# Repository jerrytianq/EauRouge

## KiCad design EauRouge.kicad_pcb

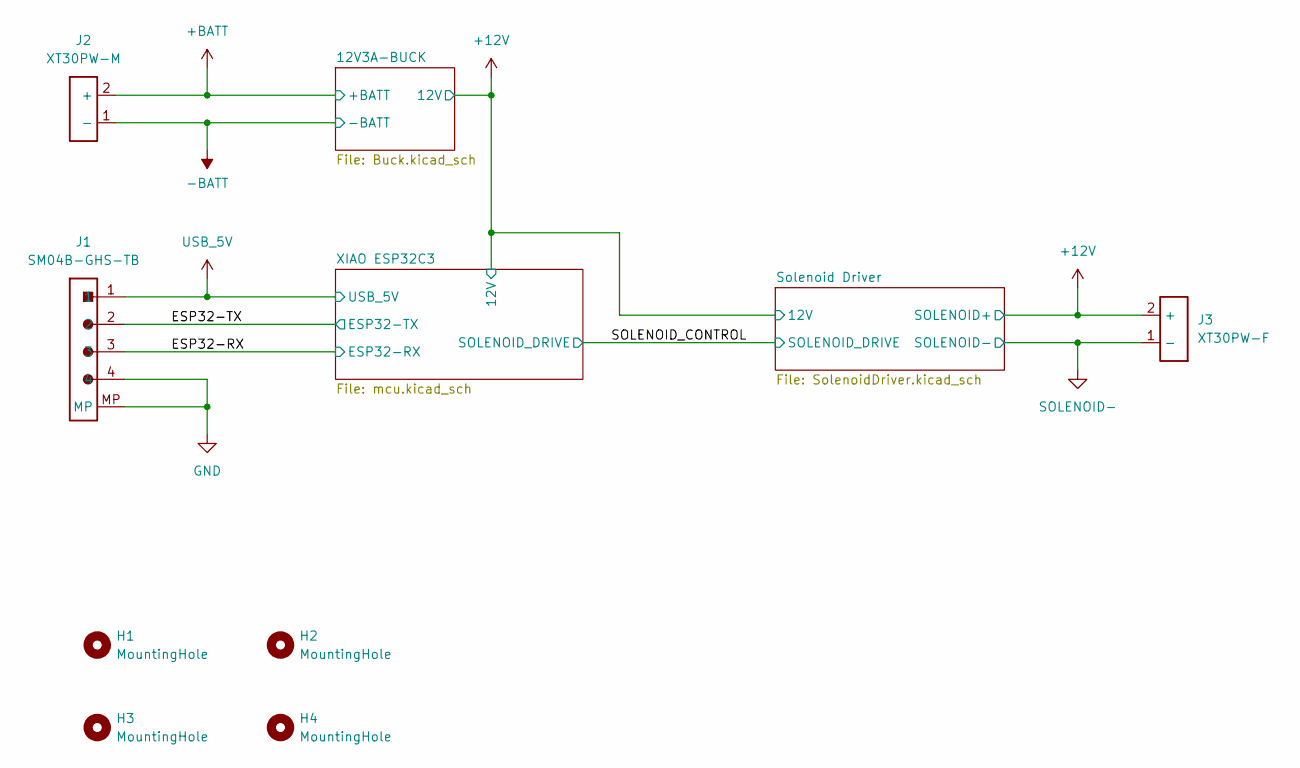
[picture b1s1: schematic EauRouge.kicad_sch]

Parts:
H1, H2, H3, H4: MountingHole; MountingHole_3.2mm_M3
J1: SM04B-GHS-TB; JST_GH_SM04B-GHS-TB_1x04-1MP_P1.25mm_Horizontal
J2: XT30PW-M; AMASS_XT30PW-M_1x02_P2.50mm_Horizontal
J3: XT30PW-F; AMASS_XT30PW-F_1x02_P2.50mm_Horizontal

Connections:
+12V: J3.2 (+); also elsewhere on the board
+BATT: J2.2 (+); also elsewhere on the board
-BATT: J2.1 (-); also elsewhere on the board
/ESP32-RX: J1.3; also elsewhere on the board
/ESP32-TX: J1.2; also elsewhere on the board
GND: J1.4, J1.MP; also elsewhere on the board
SOLENOID-: J3.1 (-); also elsewhere on the board
USB_5V: J1.1; also elsewhere on the board

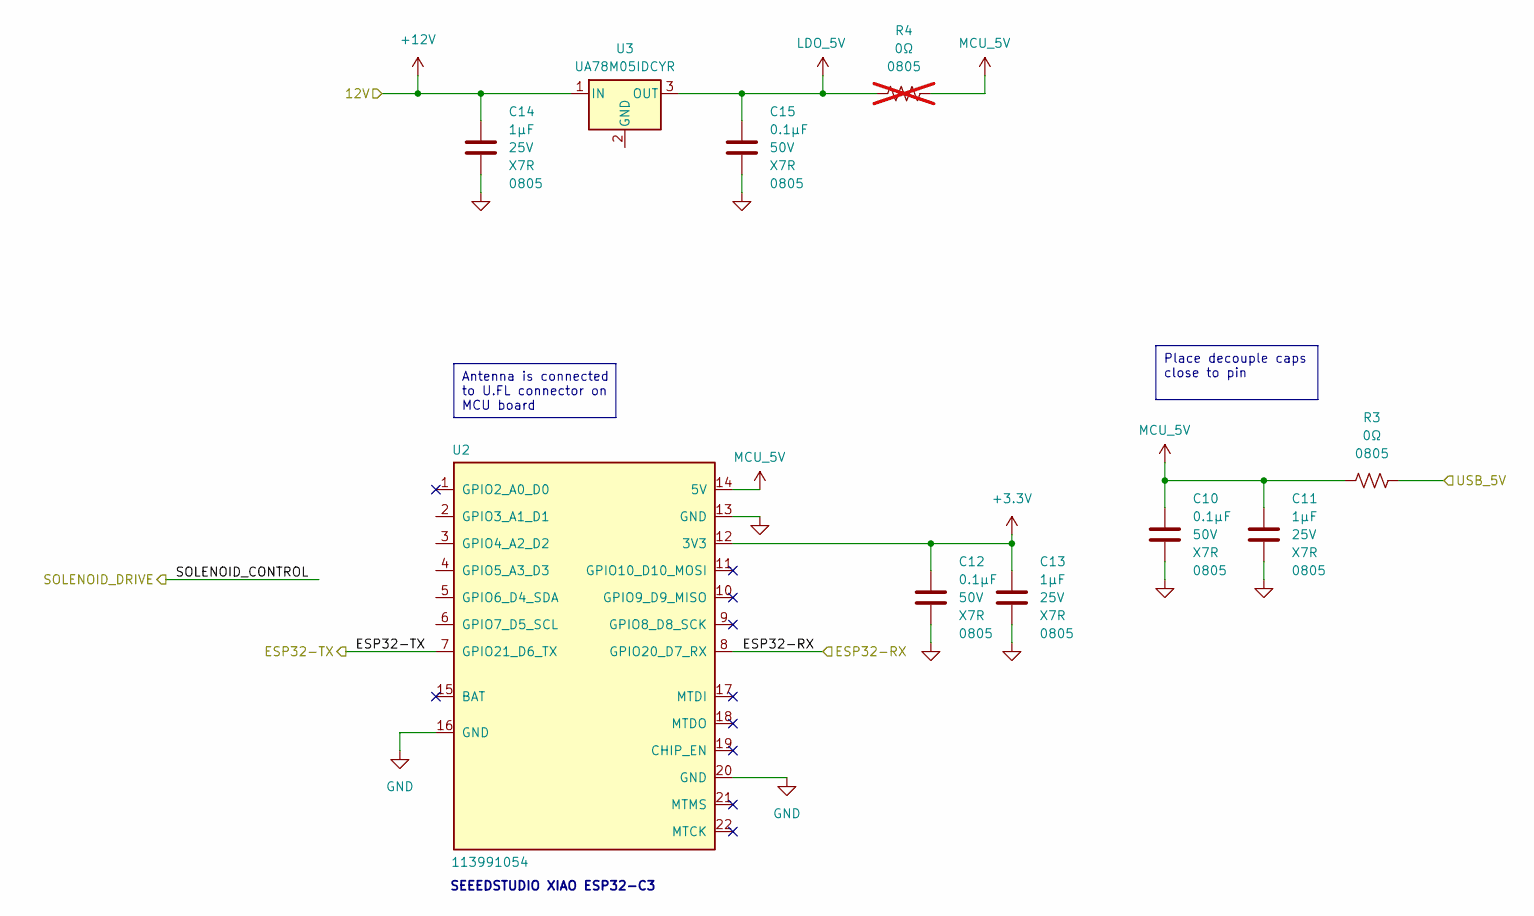
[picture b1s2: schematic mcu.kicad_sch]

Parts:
C10, C12, C15: CL21B104KBCNNNC; C_0805_2012Metric_Pad1.18x1.45mm_HandSolder; Rated Voltage 50V
C11, C13, C14: CL21B105KAFNNNE; C_0805_2012Metric_Pad1.18x1.45mm_HandSolder; Rated Voltage 25V
R3: RC0805JR-070RL; R_0805_2012Metric_Pad1.20x1.40mm_HandSolder; PARTREV V.12
R4: RC0805JR-070RL; R_0805_2012Metric_Pad1.20x1.40mm_HandSolder; PARTREV V.12; not fitted
U2: 113991054; XIAO-ESP32C3-SMD
U3: UA78M05IDCYR; SOT-223-3_TabPin2_UA78M05IDCYR

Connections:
+3.3V: C12.1, C13.1, U2.12 (3V3)
+12V: C14.1, U3.1 (IN); also elsewhere on the board
/ESP32-RX: U2.8 (GPIO20_D7_RX); also elsewhere on the board
/ESP32-TX: U2.7 (GPIO21_D6_TX); also elsewhere on the board
GND: C10.2, C11.2, C12.2, C13.2, C14.2, C15.2, U2.13 (GND), U2.16 (GND), U2.20 (GND); also elsewhere on the board
LDO_5V: C15.1, R4.1, U3.3 (OUT)
MCU_5V: C10.1, C11.1, R3.1, R4.2, U2.14 (5V)
USB_5V: R3.2; also elsewhere on the board

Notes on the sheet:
Antenna is connected to U.FL connector on MCU board
Place decouple caps close to pin
SEEEDSTUDIO XIAO ESP32-C3

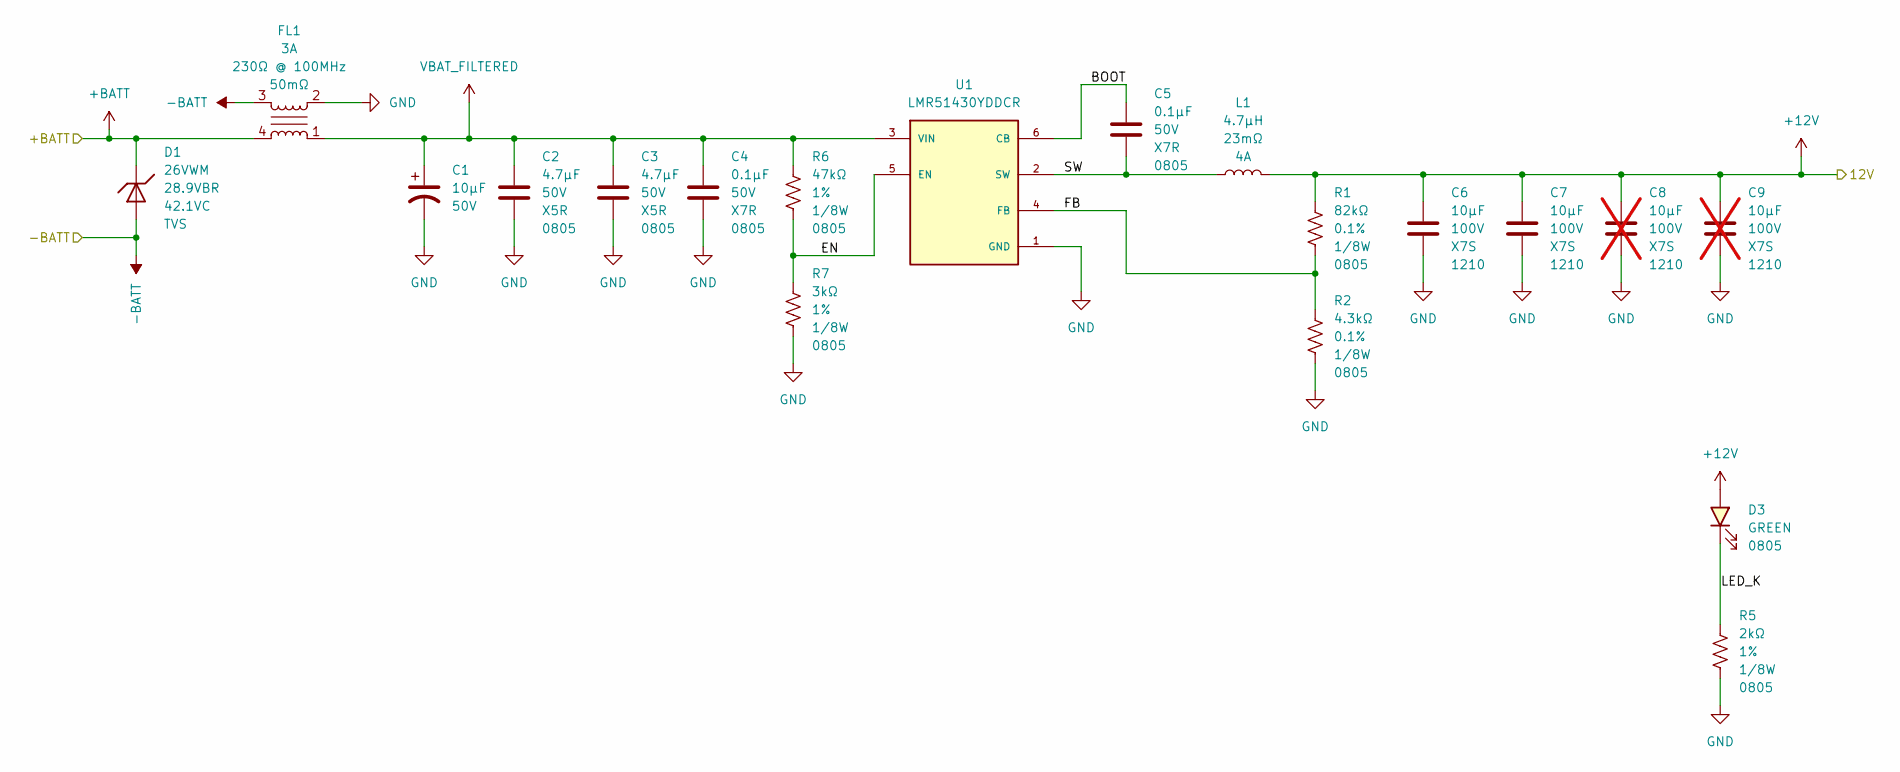
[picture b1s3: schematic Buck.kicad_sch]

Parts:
C1: 865080642006; Voltage - Rated 50V
C2, C3: GRM21BR61H475KE51L; C_0805_2012Metric_Pad1.18x1.45mm_HandSolder; Rated Voltage 50V
C4, C5: CL21B104KBCNNNC; C_0805_2012Metric_Pad1.18x1.45mm_HandSolder; Rated Voltage 50V
C6, C7: GRM32EC72A106KE05L; C_1210_3225Metric_Pad1.33x2.70mm_HandSolder; Rated Voltage 100V
C8, C9: GRM32EC72A106KE05L; C_1210_3225Metric_Pad1.33x2.70mm_HandSolder; Rated Voltage 100V; not fitted
D1: SMAJ26A-13-F; D_SMAJ26A-13-F; Voltage - Reverse Stand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 26VWM; Voltage - Breakdown (Mi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 28.9VBR
D3: APT2012CGCK; LED_0805_APT2012CGCK
FL1: ACM4520-231-2P-T000; L_CommonModeChoke_TDK_ACM4520-2P; Current Rating 3A
L1: 1255AY-4R7M=P3; L_Murata_DG6045C; Current Rating 4A
R1: RT0805BRD0782KL; R_0805_2012Metric_Pad1.20x1.40mm_HandSolder; Tolerance 0.1%
R2: RT0805BRD074K3L; R_0805_2012Metric_Pad1.20x1.40mm_HandSolder; Tolerance 0.1%
R5: RC0805FR-072KL; R_0805_2012Metric_Pad1.20x1.40mm_HandSolder; Tolerance 1%
R6: RC0805FR-0747KL; R_0805_2012Metric_Pad1.20x1.40mm_HandSolder; Tolerance 1%
R7: RC0805FR-073KL; R_0805_2012Metric_Pad1.20x1.40mm_HandSolder; Tolerance 1%
U1: LMR51430YDDCR; SOT-23_LMR514?0

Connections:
+12V: C6.1, C7.1, C8.1, C9.1, D3.2 (A), L1.2, R1.1; also elsewhere on the board
+BATT: D1.1 (C), FL1.4; also elsewhere on the board
-BATT: D1.2 (A), FL1.3; also elsewhere on the board
/12V3A-BUCK/BOOT: C5.1, U1.6 (CB)
/12V3A-BUCK/EN: R6.2, R7.1, U1.5 (EN)
/12V3A-BUCK/FB: R1.2, R2.1, U1.4 (FB)
/12V3A-BUCK/LED_K: D3.1 (K), R5.1
/12V3A-BUCK/SW: C5.2, L1.1, U1.2 (SW)
GND: C1.2, C2.2, C3.2, C4.2, C6.2, C7.2, C8.2, C9.2, FL1.2, R2.2, R5.2, R7.2, U1.1 (GND); also elsewhere on the board
VBAT_FILTERED: C1.1, C2.1, C3.1, C4.1, FL1.1, R6.1, U1.3 (VIN)

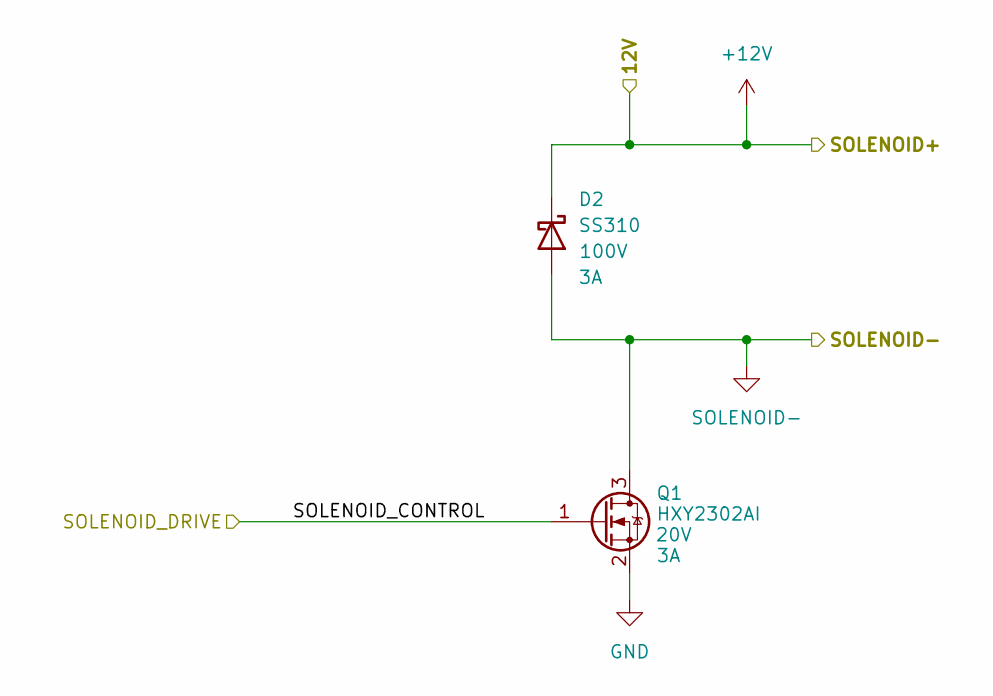
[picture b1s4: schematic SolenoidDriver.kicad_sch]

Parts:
D2: SS310; D_SMA_MDD_DO-214AC_SMA
Q1: HXY2302AI; SOT-23-3_HXY2302AI

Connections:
+12V: D2.1 (K); also elsewhere on the board
/SOLENOID_CONTROL: Q1.1 (G)
GND: Q1.2 (S); also elsewhere on the board
SOLENOID-: D2.2 (A), Q1.3 (D); also elsewhere on the board

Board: 2 copper layers, 36 parts (1 on the bottom side), 17 nets, no tracks yet.

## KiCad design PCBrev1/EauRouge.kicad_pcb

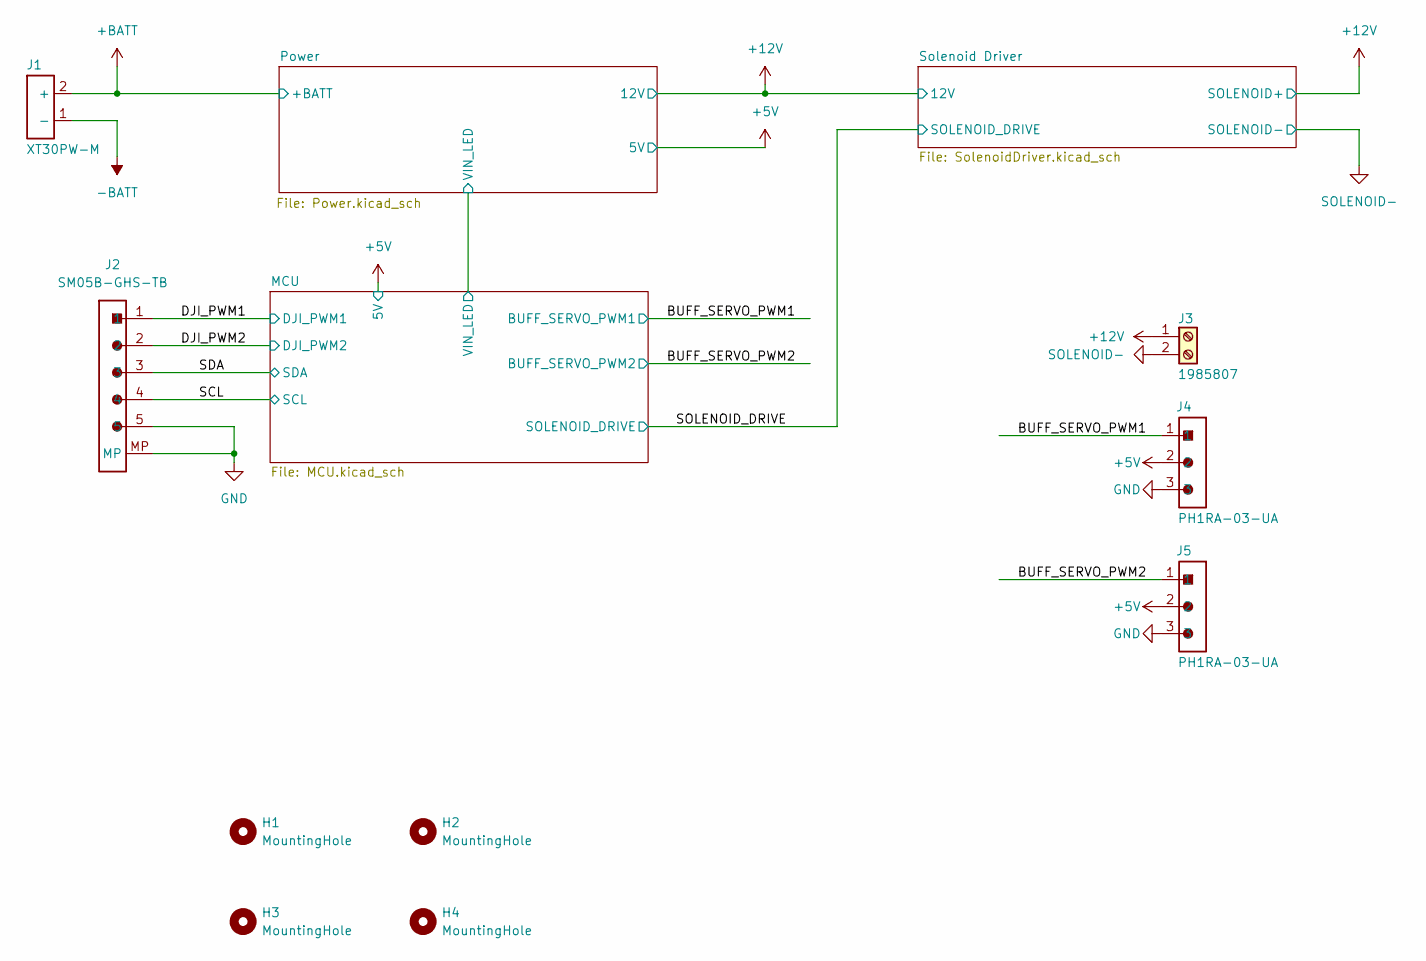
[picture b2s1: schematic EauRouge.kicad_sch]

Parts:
H1, H2, H3, H4: MountingHole; MountingHole_3.2mm_M3
J1: XT30PW-M; AMASS_XT30PW-M_1x02_P2.50mm_Horizontal
J2: SM05B-GHS-TB; JST_GH_SM05B-GHS-TB_1x05-1MP_P1.25mm_Horizontal
J3: 1985807; TerminalBlock_Phoenix_MKDS-1,5-2_1x02_P3.50mm_Horizontal_19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
J4, J5: PH1RA-03-UA; PinHeader_1x03_P2.54mm_Horizontal

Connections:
+5V: J4.2, J5.2; also elsewhere on the board
+12V: J3.1; also elsewhere on the board
+BATT: J1.2 (+); also elsewhere on the board
-BATT: J1.1 (-); also elsewhere on the board
/BUFF_SERVO_PWM1: J4.1; also elsewhere on the board
/BUFF_SERVO_PWM2: J5.1; also elsewhere on the board
/DJI_PWM1: J2.1; also elsewhere on the board
/DJI_PWM2: J2.2; also elsewhere on the board
/SCL: J2.4; also elsewhere on the board
/SDA: J2.3; also elsewhere on the board
GND: J2.5, J2.MP, J4.3, J5.3; also elsewhere on the board
SOLENOID-: J3.2; also elsewhere on the board

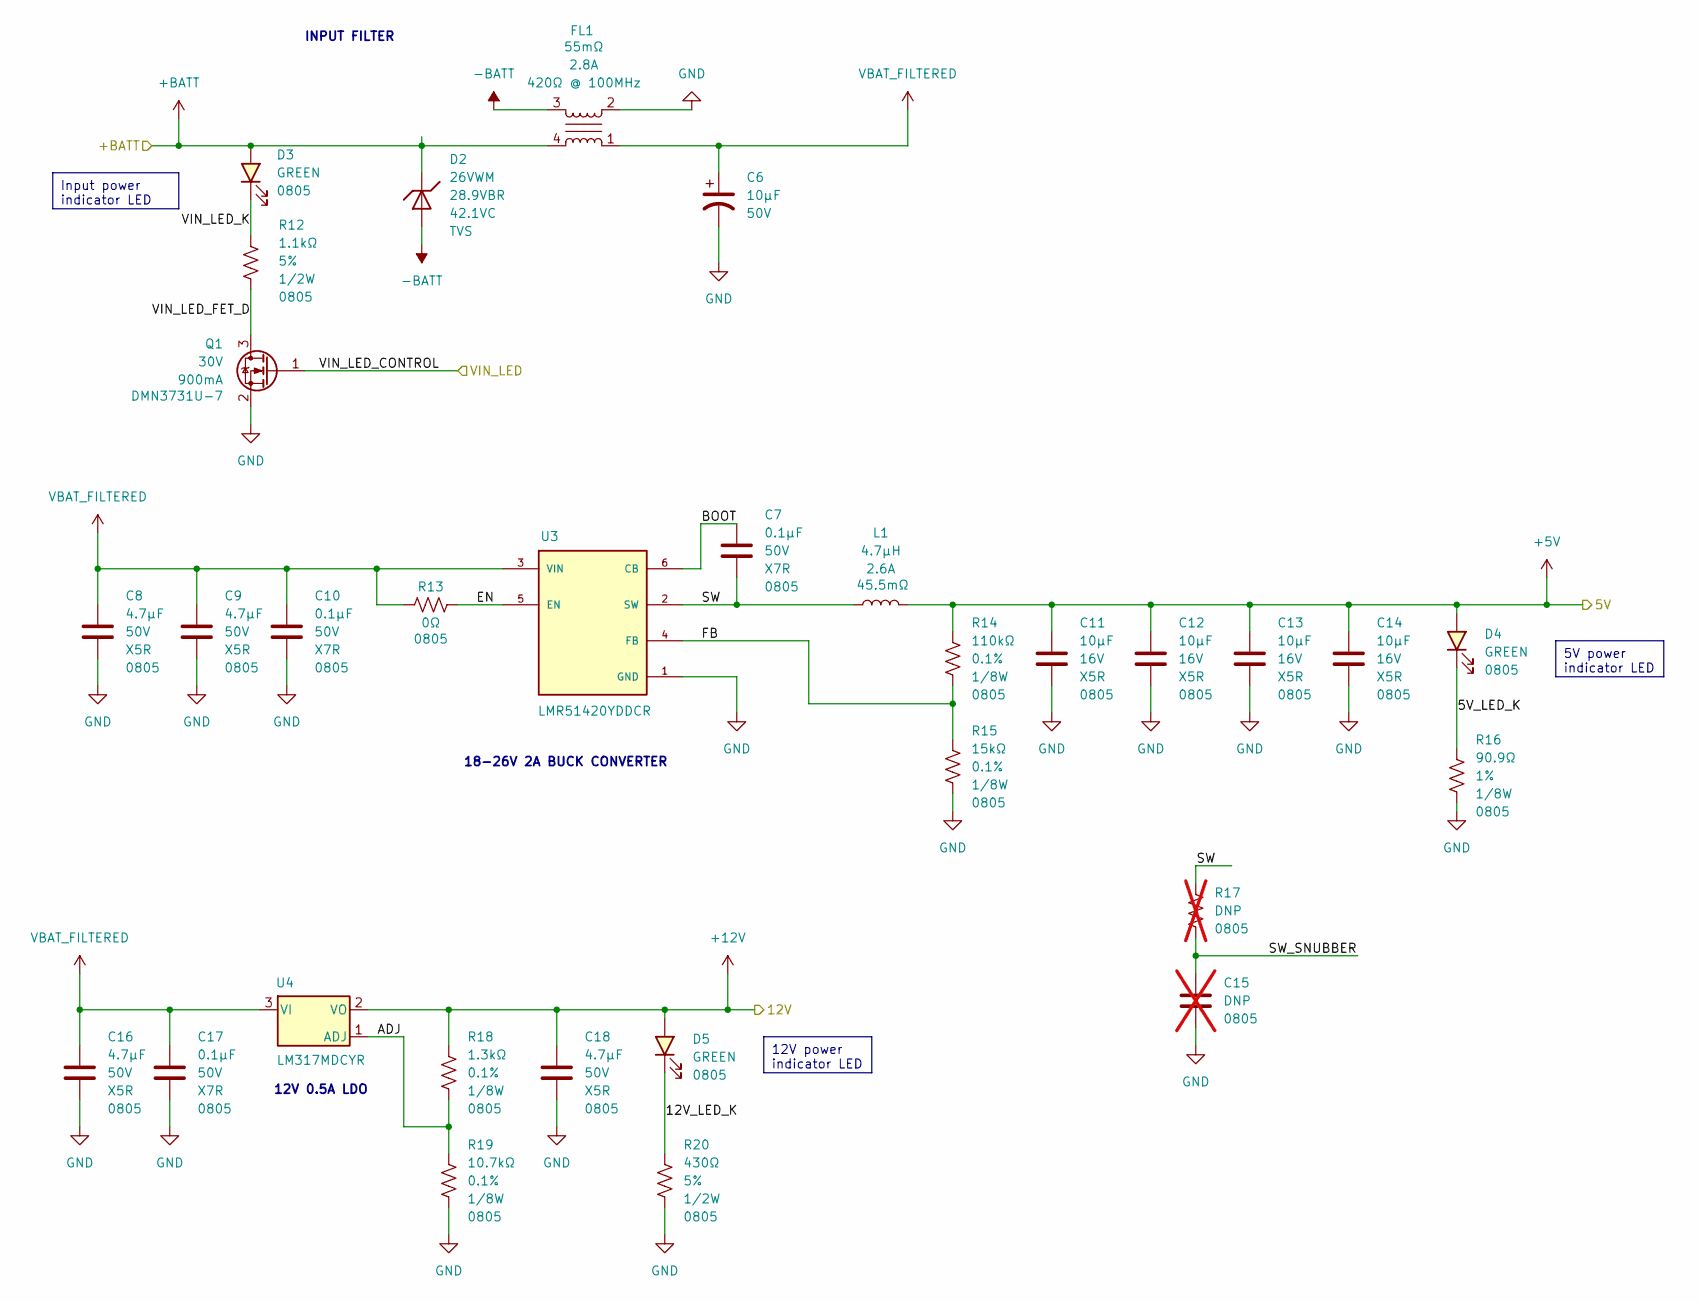
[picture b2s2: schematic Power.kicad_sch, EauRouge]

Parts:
C6: 865080642006; Voltage - Rated 50V
C7, C10, C17: CL21B104KBCNNNC; C_0805_2012Metric_Pad1.18x1.45mm_HandSolder; Rated Voltage 50V
C8, C9, C16, C18: GRM21BR61H475KE51L; C_0805_2012Metric_Pad1.18x1.45mm_HandSolder; Rated Voltage 50V
C11, C12, C13, C14: GRM21BR61C106KE15K; C_0805_2012Metric_Pad1.18x1.45mm_HandSolder; Rated Voltage 16V
C15: DNP; C_0805_2012Metric_Pad1.18x1.45mm_HandSolder; not fitted
D2: SMAJ26A-13-F; D_SMAJ26A-13-F; Voltage - Reverse Stand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 26VWM; Voltage - Breakdown (Mi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 28.9VBR
D3, D4, D5: 150080GS75000; LED_0805_2012Metric_Pad1.15x1.40mm_HandSolder
FL1: ACM4520-421-2P-T000; L_CommonModeChoke_TDK_ACM4520-421-2P-T000; Current Rating 2.8A
L1: NRS5030T4R7MMGJV; L_Taiyo-Yuden_NRS5030T4R7MMGJV; Current Rating 2.6A
Q1: DMN3731U-7; SOT-23-3_DMN3731U-7
R12: ERJ-P06J112V; R_0805_2012Metric_Pad1.20x1.40mm_HandSolder; Tolerance 5%
R13: RC0805JR-070RL; R_0805_2012Metric_Pad1.20x1.40mm_HandSolder; PARTREV V.12
R14: ERA-6AEB114V; R_0805_2012Metric_Pad1.20x1.40mm_HandSolder; Tolerance 0.1%; PARTREV V.12
R15: RT0805BRD0715KL; R_0805_2012Metric_Pad1.20x1.40mm_HandSolder; Tolerance 0.1%; PARTREV V.12
R16: RC0805FR-0790R9L; R_0805_2012Metric_Pad1.20x1.40mm_HandSolder; Tolerance 1%
R17: DNP 0805; R_0805_2012Metric_Pad1.20x1.40mm_HandSolder; PARTREV V.12; not fitted
R18: RT0805BRD071K3L; R_0805_2012Metric_Pad1.20x1.40mm_HandSolder; Tolerance 0.1%
R19: RT0805BRD0710K7L; R_0805_2012Metric_Pad1.20x1.40mm_HandSolder; Tolerance 0.1%
R20: ERJ-P06J431V; R_0805_2012Metric_Pad1.20x1.40mm_HandSolder; Tolerance 5%
U3: LMR51420YDDCR; SOT-23-6_LMR51420YDDCR; PARTREV C
U4: LM317MDCYR; SOT-223-3_TabPin2_LM317MDCYR

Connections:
+5V: C11.1, C12.1, C13.1, C14.1, D4.2 (A), L1.2, R14.1; also elsewhere on the board
+12V: C18.1, D5.2 (A), R18.1, U4.2 (VO); also elsewhere on the board
+BATT: D2.1 (C), D3.2 (A), FL1.4; also elsewhere on the board
-BATT: D2.2 (A), FL1.3; also elsewhere on the board
/MCU/VIN_LED_CONTROL: Q1.1 (G); also elsewhere on the board
/Power/5V_LED_K: D4.1 (K), R16.1
/Power/12V_LED_K: D5.1 (K), R20.1
/Power/ADJ: R18.2, R19.1, U4.1 (ADJ)
/Power/BOOT: C7.1, U3.6 (CB)
/Power/EN: R13.2, U3.5 (EN)
/Power/FB: R14.2, R15.1, U3.4 (FB)
/Power/SW: C7.2, L1.1, R17.1, U3.2 (SW)
/Power/SW_SNUBBER: C15.1, R17.2
/Power/VIN_LED_FET_D: Q1.3 (D), R12.2
/Power/VIN_LED_K: D3.1 (K), R12.1
GND: C6.2, C8.2, C9.2, C10.2, C11.2, C12.2, C13.2, C14.2, C15.2, C16.2, C17.2, C18.2, FL1.2, Q1.2 (S), R15.2, R16.2, R19.2, R20.2, U3.1 (GND); also elsewhere on the board
VBAT_FILTERED: C6.1, C8.1, C9.1, C10.1, C16.1, C17.1, FL1.1, R13.1, U3.3 (VIN), U4.3 (VI)

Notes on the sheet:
12V power indicator LED
Input power indicator LED
5V power indicator LED
12V 0.5A LDO
18-26V 2A BUCK CONVERTER
INPUT FILTER

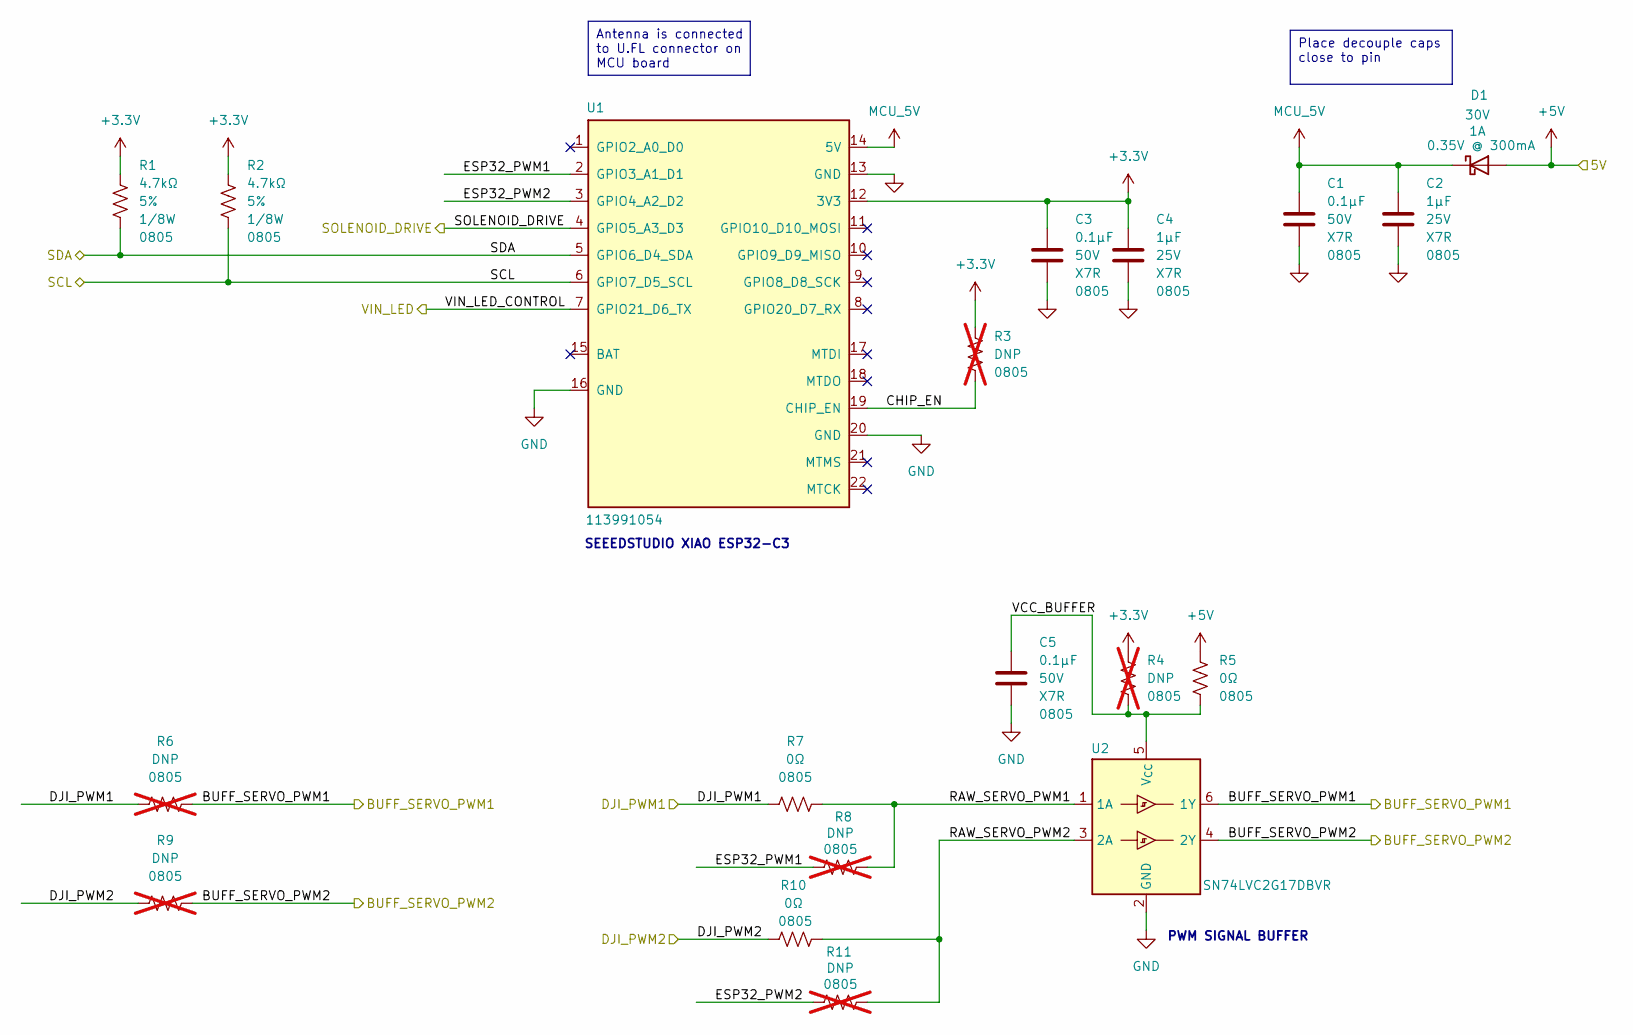
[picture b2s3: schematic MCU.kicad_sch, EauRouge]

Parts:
C1, C3, C5: CL21B104KBCNNNC; C_0805_2012Metric_Pad1.18x1.45mm_HandSolder; Rated Voltage 50V
C2, C4: CL21B105KAFNNNE; C_0805_2012Metric_Pad1.18x1.45mm_HandSolder; Rated Voltage 25V
D1: MSS1P3L-M3/89A; D_MicroSMP_AK_MSS1P3L-M3_89A; Voltage - DC Reverse (V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 30V; Forward Voltage Drop @ 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 0.35V @ 300mA
R1, R2: RMCF0805JT4K70; R_0805_2012Metric_Pad1.20x1.40mm_HandSolder; Tolerance 5%; PARTREV V.12
R3, R4, R6, R8, R9, R11: DNP 0805; R_0805_2012Metric_Pad1.20x1.40mm_HandSolder; PARTREV V.12; not fitted
R5, R7, R10: RC0805JR-070RL; R_0805_2012Metric_Pad1.20x1.40mm_HandSolder; PARTREV V.12
U1: 113991054; XIAO-ESP32C3-SMD
U2: SN74LVC2G17DBVR; SOT-23-6

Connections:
+3.3V: C3.1, C4.1, R1.1, R2.1, R3.2, R4.1, U1.12 (3V3)
+5V: D1.2 (A), R5.1; also elsewhere on the board
/BUFF_SERVO_PWM1: R6.2, U2.6 (1Y); also elsewhere on the board
/BUFF_SERVO_PWM2: R9.2, U2.4 (2Y); also elsewhere on the board
/DJI_PWM1: R6.1, R7.1; also elsewhere on the board
/DJI_PWM2: R9.1, R10.1; also elsewhere on the board
/MCU/CHIP_EN: R3.1, U1.19 (CHIP_EN)
/MCU/ESP32_PWM1: R8.1, U1.2 (GPIO3_A1_D1)
/MCU/ESP32_PWM2: R11.1, U1.3 (GPIO4_A2_D2)
/MCU/RAW_SERVO_PWM1: R7.2, R8.2, U2.1 (1A)
/MCU/RAW_SERVO_PWM2: R10.2, R11.2, U2.3 (2A)
/MCU/VCC_BUFFER: C5.1, R4.2, R5.2, U2.5 (V_{CC})
/MCU/VIN_LED_CONTROL: U1.7 (GPIO21_D6_TX); also elsewhere on the board
/SCL: R2.2, U1.6 (GPIO7_D5_SCL); also elsewhere on the board
/SDA: R1.2, U1.5 (GPIO6_D4_SDA); also elsewhere on the board
/SOLENOID_DRIVE: U1.4 (GPIO5_A3_D3); also elsewhere on the board
GND: C1.2, C2.2, C3.2, C4.2, C5.2, U1.13 (GND), U1.16 (GND), U1.20 (GND), U2.2 (GND); also elsewhere on the board
MCU_5V: C1.1, C2.1, D1.1 (K), U1.14 (5V)

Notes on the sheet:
Place decouple caps close to pin
Antenna is connected to U.FL connector on MCU board
SEEEDSTUDIO XIAO ESP32-C3
PWM SIGNAL BUFFER

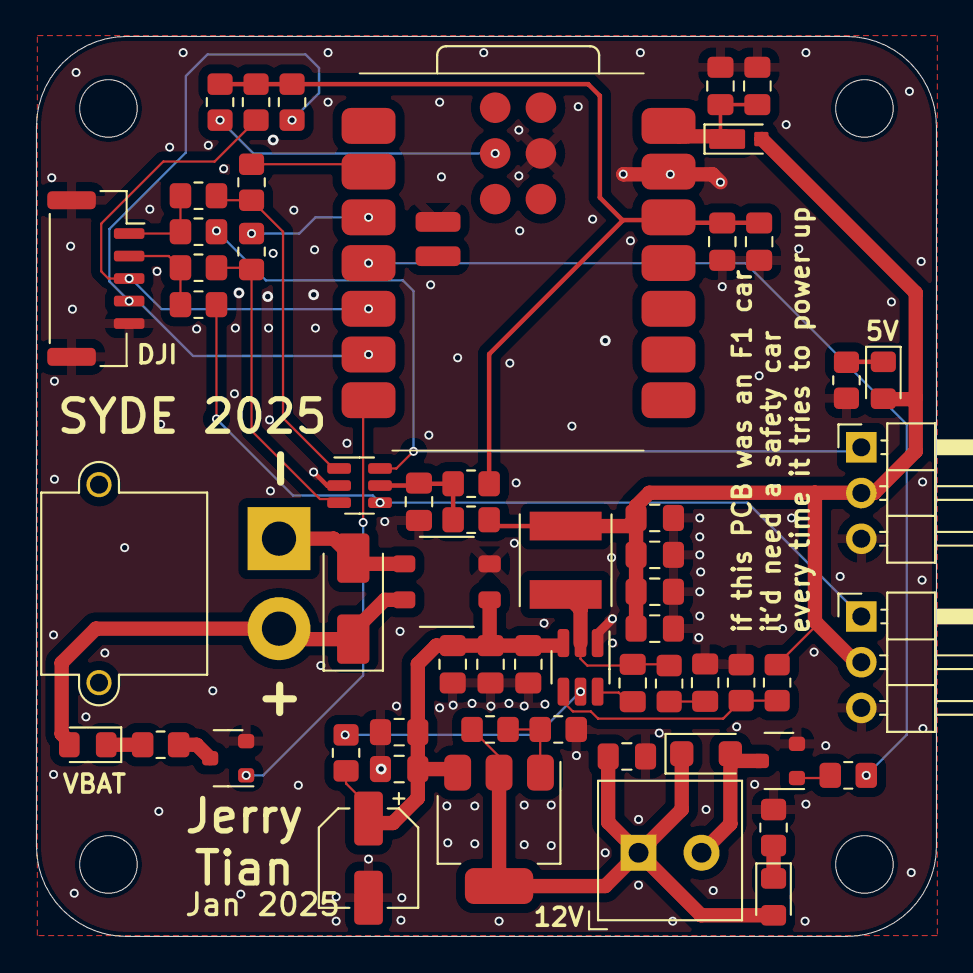
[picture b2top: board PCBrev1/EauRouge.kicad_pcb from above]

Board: 4 copper layers, 50.0 x 50.0 mm, 62 parts (0 on the bottom side), 34 nets.

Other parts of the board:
D6: STPS2H100ZF; D_SOD-123F_STPS2H100ZF
Q2: DMN3731U-7; SOT-23-3_DMN3731U-7
R21: RC0805JR-070RL; R_0805_2012Metric_Pad1.20x1.40mm_HandSolder

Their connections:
+12V: D6.1 (K); also elsewhere on the board
/SOLENOID_DRIVE: R21.1; also elsewhere on the board
/Solenoid Driver/SOLENOID_FET_G: Q2.1 (G), R21.2
GND: Q2.2 (S); also elsewhere on the board
SOLENOID-: D6.2 (A), Q2.3 (D); also elsewhere on the board

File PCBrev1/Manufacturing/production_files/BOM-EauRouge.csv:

Comment,Designator,Footprint,LCSC,Quantity
RC0805JR-070RL,R10,R_0805_2012Metric_Pad1.20x1.40mm_HandSolder,,1
GRM21BR61C106KE15K,C11,C_0805_2012Metric_Pad1.18x1.45mm_HandSolder,,1
CL21B104KBCNNNC,C17,C_0805_2012Metric_Pad1.18x1.45mm_HandSolder,,1
CL21B105KAFNNNE,C4,C_0805_2012Metric_Pad1.18x1.45mm_HandSolder,,1
ERA-6AEB114V,R14,R_0805_2012Metric_Pad1.20x1.40mm_HandSolder,,1
MSS1P3L-M3/89A,D1,D_MicroSMP_AK_MSS1P3L-M3_89A,,1
GRM21BR61H475KE51L,C18,C_0805_2012Metric_Pad1.18x1.45mm_HandSolder,,1
GRM21BR61H475KE51L,C9,C_0805_2012Metric_Pad1.18x1.45mm_HandSolder,,1
RT0805BRD0710K7L,R19,R_0805_2012Metric_Pad1.20x1.40mm_HandSolder,,1
865080642006,C6,865081000000,,1
SMAJ26A-13-F,D2,D_SMAJ26A-13-F,,1
CL21B105KAFNNNE,C2,C_0805_2012Metric_Pad1.18x1.45mm_HandSolder,,1
GRM21BR61H475KE51L,C8,C_0805_2012Metric_Pad1.18x1.45mm_HandSolder,,1
113991054,U1,XIAO-ESP32C3-SMD,,1
CL21B104KBCNNNC,C1,C_0805_2012Metric_Pad1.18x1.45mm_HandSolder,,1
150080GS75000,D4,LED_0805_2012Metric_Pad1.15x1.40mm_HandSolder,,1
ERJ-P06J112V,R12,R_0805_2012Metric_Pad1.20x1.40mm_HandSolder,,1
PH1RA-03-UA,J4,PinHeader_1x03_P2.54mm_Horizontal,,1
150080GS75000,D5,LED_0805_2012Metric_Pad1.15x1.40mm_HandSolder,,1
STPS2H100ZF,D6,D_SOD-123F_STPS2H100ZF,,1
GRM21BR61H475KE51L,C16,C_0805_2012Metric_Pad1.18x1.45mm_HandSolder,,1
LM317MDCYR,U4,SOT-223-3_TabPin2_LM317MDCYR,,1
XT30PW-M,J1,AMASS_XT30PW-M_1x02_P2.50mm_Horizontal,,1
RC0805FR-0790R9L,R16,R_0805_2012Metric_Pad1.20x1.40mm_HandSolder,,1
RT0805BRD071K3L,R18,R_0805_2012Metric_Pad1.20x1.40mm_HandSolder,,1
GRM21BR61C106KE15K,C14,C_0805_2012Metric_Pad1.18x1.45mm_HandSolder,,1
RC0805JR-070RL,R21,R_0805_2012Metric_Pad1.20x1.40mm_HandSolder,,1
DMN3731U-7,Q1,SOT-23-3_DMN3731U-7,,1
ERJ-P06J112V,R20,R_0805_2012Metric_Pad1.20x1.40mm_HandSolder,,1
LMR51420YDDCR,U3,SOT-23-6_LMR51420YDDCR,,1
GRM21BR61C106KE15K,C13,C_0805_2012Metric_Pad1.18x1.45mm_HandSolder,,1
CL21B104KBCNNNC,C3,C_0805_2012Metric_Pad1.18x1.45mm_HandSolder,,1
DMN3731U-7,Q2,SOT-23-3_DMN3731U-7,,1
RT0805BRD0715KL,R15,R_0805_2012Metric_Pad1.20x1.40mm_HandSolder,,1
GRM21BR61C106KE15K,C12,C_0805_2012Metric_Pad1.18x1.45mm_HandSolder,,1
RC0805JR-070RL,R13,R_0805_2012Metric_Pad1.20x1.40mm_HandSolder,,1
ACM4520-421-2P-T000,FL1,L_CommonModeChoke_TDK_ACM4520-421-2P-T000,,1
CL21B104KBCNNNC,C7,C_0805_2012Metric_Pad1.18x1.45mm_HandSolder,,1
RC0805JR-070RL,R7,R_0805_2012Metric_Pad1.20x1.40mm_HandSolder,,1
SM05B-GHS-TB,J2,JST_GH_SM05B-GHS-TB_1x05-1MP_P1.25mm_Horizontal,,1
NRS5030T4R7MMGJV,L1,L_Taiyo-Yuden_NRS5030T4R7MMGJV,,1
RMCF0805JT4K70,R1,R_0805_2012Metric_Pad1.20x1.40mm_HandSolder,,1
1985807,J3,"TerminalBlock_Phoenix_MKDS-1,5-2_1x02_P3.50mm_Horizontal_1985807",,1
RMCF0805JT4K70,R2,R_0805_2012Metric_Pad1.20x1.40mm_HandSolder,,1
150080GS75000,D3,LED_0805_2012Metric_Pad1.15x1.40mm_HandSolder,,1
RC0805JR-070RL,R5,R_0805_2012Metric_Pad1.20x1.40mm_HandSolder,,1
CL21B104KBCNNNC,C10,C_0805_2012Metric_Pad1.18x1.45mm_HandSolder,,1
SN74LVC2G17DBVR,U2,SOT-23-6,,1
CL21B104KBCNNNC,C5,C_0805_2012Metric_Pad1.18x1.45mm_HandSolder,,1
PH1RA-03-UA,J5,PinHeader_1x03_P2.54mm_Horizontal,,1

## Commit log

2025-01-14 drew buck circuit
2025-01-16 added CMC, TVS diode, electrolytic cap at buck input to improve inrush current effects
2025-01-17 Added solenoid driver circuit
2025-01-18 1st round of rough component placement
2025-01-19 pcb routing completed
2025-01-25 added i2c + another servo rail
2025-01-28 2nd rev is done
2025-01-28 added new memes
2025-01-28 changed meme silkscreen
2025-01-28 rename proj
2025-01-29 removed duplicated pullup resistor on chip en
2025-01-30 ordered PCB
2025-01-30 generated backup schematic pdfs
2025-03-12 added uart rx arduino code
2025-03-16 starting PCB rev 2 with perf board prototype
2025-03-24 fydp board rev2 starting component placement
